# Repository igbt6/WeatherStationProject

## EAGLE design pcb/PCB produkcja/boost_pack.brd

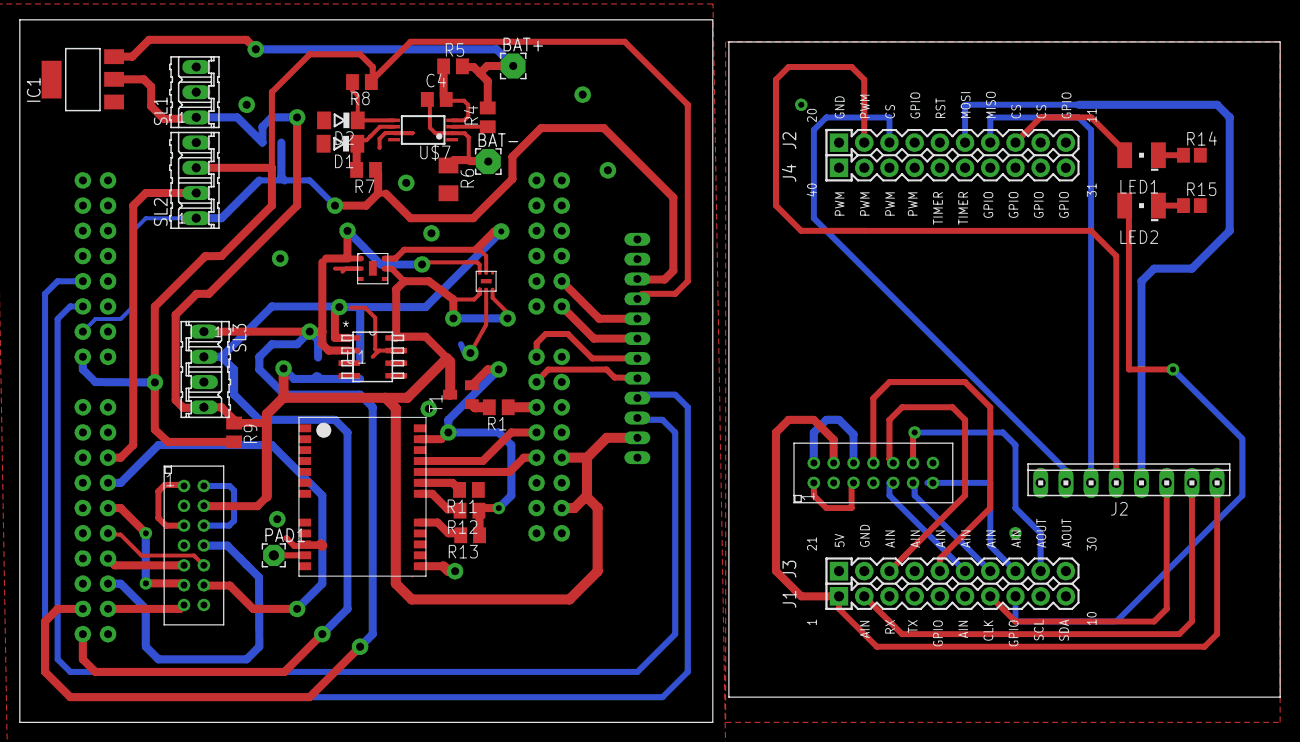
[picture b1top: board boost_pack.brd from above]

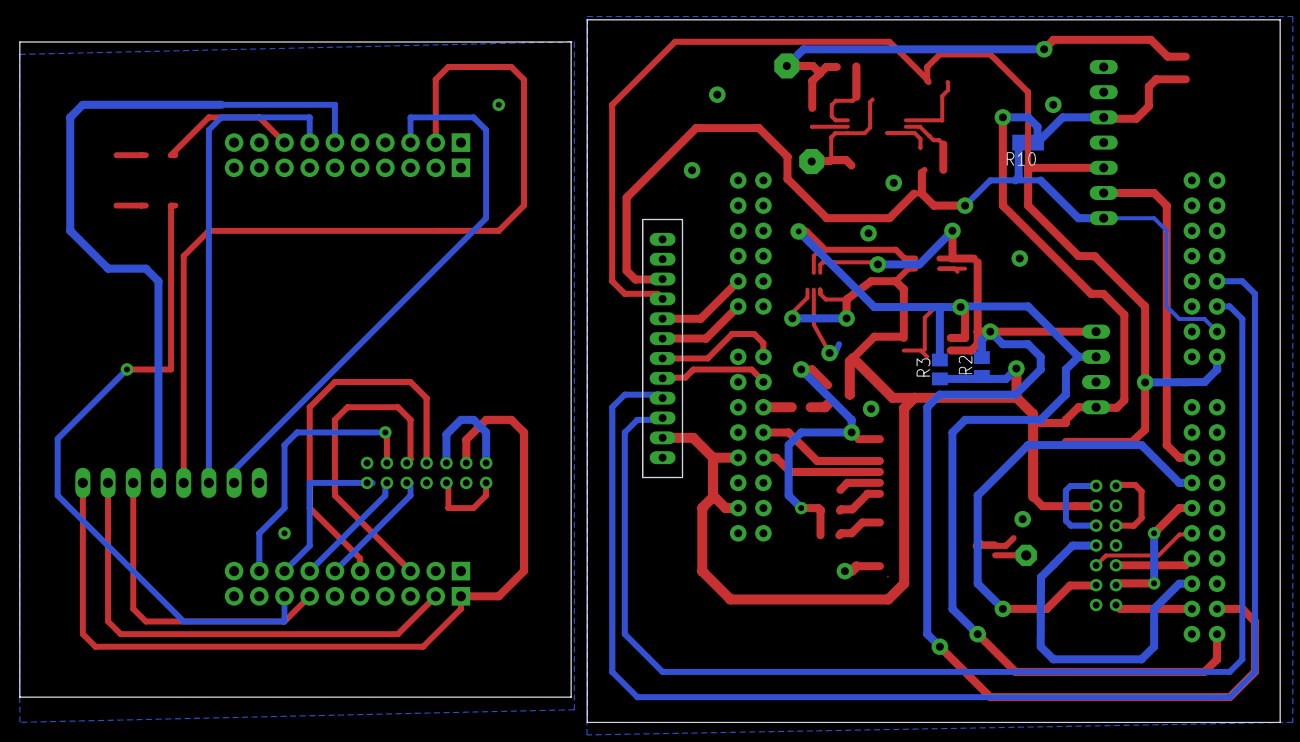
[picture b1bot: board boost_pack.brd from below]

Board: 2 copper layers, 127.0 x 70.8 mm, 39 parts (3 on the bottom side), 56 nets.

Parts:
A1: 4X10-BOOSTERPACK
BAT+: 2,54/0,8
BAT-: 2,54/0,8
C4: 100n; C0805
D1, D2: 5V6; SOD80C
IC1: REG1117; SOT223
J2: 10X08MTA
LED1, LED2: LG_T679-E1F1-1; PLCC2
PAD1: 2,15/1,0
R1, R11, R12, R13: 1K; M0805
R2, R3, R9, R10: 10K; M0805
R4: 1k; M0805
R5: 500R; M0805
R6: 20m; M1206
R7, R8: 150R; M0805
R14, R15: R0805
SL1: 03P
SL2, SL3: 04P
T1: SOT23-BCE
U1: ADT7410TRZ; R_8
U$1: INTO_CON
U$2: GTS-4E-60
U$3, U$8: 2X7PIN; 2X7PINCON
U$4: SI7020-A10; DFN6(3X3MM)
U$5: 12PINCON; 12PIN2MMCON
U$6: MAX44006; 6OTDFN
U$7: DS2782; TSSOP8

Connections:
+3V3: A1.1, J2.1, U$8.P$13
+5V/1: IC1.2, R2.1, R3.1, R9.1, R10.1, SL1.1, SL3.4, T1.E, U1.8, U$1.P$39, U$1.P$43, U$3.P$13, U$4.P$5, U$5.P$2, U$6.P1, U$6.P3
GND: D1.A, D2.A, IC1.1, R6.2, R11.1, SL2.4, SL3.3, U1.3, U1.4, U1.7, U$1.P$30, U$1.P$47, U$1.P$49, U$2.A10, U$2.A12, U$2.A13, U$2.A24, U$3.P$2, U$3.P$8, U$4.P$2, U$5.P$1, U$6.P2, U$7.7
GND1: A1.20, A1.22, J2.8, R14.2, R15.2, U$8.P$2, U$8.P$8
INTER: SL2.2, U$1.P$21
unnamed: U$1.P$46, U$2.A21
unnamed: U$8.P$12, U$8.P$14
unnamed: U$1.P$52, U$5.P$6
unnamed: PAD1.1, U$2.A11
unnamed: U$1.P$50, U$5.P$5
unnamed: U$1.P$53, U$5.P$7
unnamed: U$1.P$55, U$5.P$8
unnamed: U$1.P$12, U$5.P$3
unnamed: U$1.P$10, U$5.P$4
unnamed: C4.2, R5.1, U$7.4
unnamed: BAT-.1, C4.1, R6.1, U$7.2
unnamed: R4.1, U$7.3
unnamed: D1.C, R7.2, U$7.6
unnamed: D2.C, R8.2, U$7.5
unnamed: U$3.P$1, U$3.P$3
unnamed: U$3.P$12, U$3.P$14
unnamed: U$1.P$25, U$3.P$6
unnamed: U$1.P$27, U$3.P$10
unnamed: BAT+.1, IC1.3, R4.2, R5.2
unnamed: U$1.P$29, U$3.P$5
unnamed: U$1.P$31, U$3.P$11
unnamed: U$1.P$23, U$3.P$9
unnamed: R12.1, R13.1, T1.C, U$2.A23
unnamed: R1.1, U$1.P$48
unnamed: R1.2, T1.B
unnamed: U$1.P$33, U$3.P$7
unnamed: U$1.P$44, U$2.A20
unnamed: R12.2, U$2.A18
unnamed: R11.2, U$2.A19
unnamed: R13.2, U$2.A17
unnamed: U$8.P$1, U$8.P$3
unnamed: LED1.C, R14.1
unnamed: LED2.C, R15.1
PA4: A1.13, LED1.A
PA5: A1.8, LED2.A
PB2: A1.19, J2.5
PB4: A1.7, J2.3
PB5: A1.2, J2.2
PB6: A1.14, J2.6
PB7: A1.15, J2.4
PD0: A1.23, U$8.P$10
PD2: A1.25, U$8.P$11
PD3: A1.26, U$8.P$5
PE0: A1.18, J2.7
PE1: A1.27, U$8.P$6
PE2: A1.28, U$8.P$7
PE3: A1.29, U$8.P$9
SCL1: R3.2, SL3.2, U1.1, U$1.P$36, U$4.P$6, U$6.P5
SCL2: R7.1, R10.2, SL2.1, U$1.P$14, U$5.P$10
SDA1: R2.2, SL3.1, U1.2, U$1.P$34, U$4.P$1, U$6.P6
SDA2: R8.1, R9.2, SL2.3, U$1.P$16, U$5.P$9

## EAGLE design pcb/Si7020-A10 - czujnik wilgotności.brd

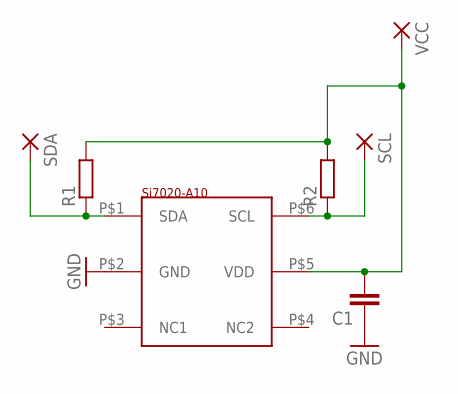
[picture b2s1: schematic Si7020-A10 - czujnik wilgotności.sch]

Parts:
C1: C-EUC0805; C0805
R1, R2: R-EU_M0805; M0805
SCL: 2,54/0,9
SDA: 2,54/0,9
U$1: SI7020-A10; DFN6(3X3MM)
VCC: 2,54/0,9

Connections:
GND: C1.1, U$1.P$2 (GND)
unnamed: C1.2, R1.2, R2.2, U$1.P$5 (VDD), VCC.1
unnamed: R2.1, SCL.1, U$1.P$6 (SCL)
unnamed: R1.1, SDA.1, U$1.P$1 (SDA)

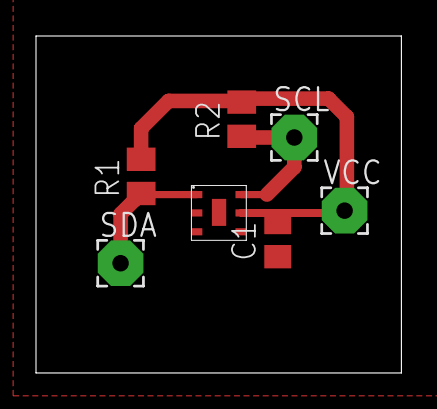
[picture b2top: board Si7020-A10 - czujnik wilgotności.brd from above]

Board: 2 copper layers, 20.3 x 18.7 mm, 7 parts (0 on the bottom side), 4 nets.

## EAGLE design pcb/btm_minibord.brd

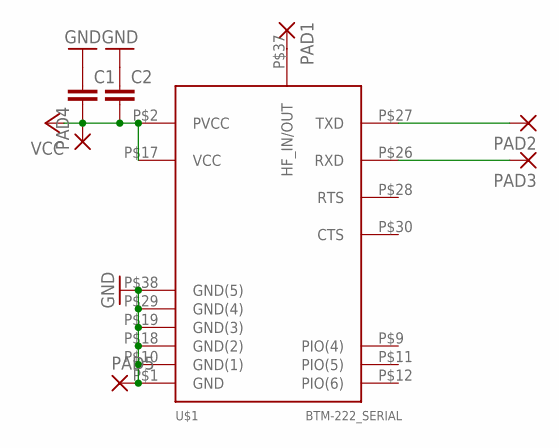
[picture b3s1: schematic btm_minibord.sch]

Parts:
C1, C2: C-EUC0805; C0805
PAD1, PAD2, PAD3, PAD4, PAD5: 1,6/0,8
U$1: BTM-222_SERIAL; BTM-222

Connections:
GND: C1.1, C2.1, PAD5.1, U$1.P$1 (GND), U$1.P$10 (GND(1)), U$1.P$18 (GND(2)), U$1.P$19 (GND(3)), U$1.P$29 (GND(4)), U$1.P$38 (GND(5))
unnamed: PAD2.1, U$1.P$27 (TXD)
unnamed: PAD3.1, U$1.P$26 (RXD)
unnamed: PAD1.1, U$1.P$37 (HF_IN/OUT)
VCC: C1.2, C2.2, PAD4.1, U$1.P$2 (PVCC), U$1.P$17 (VCC)

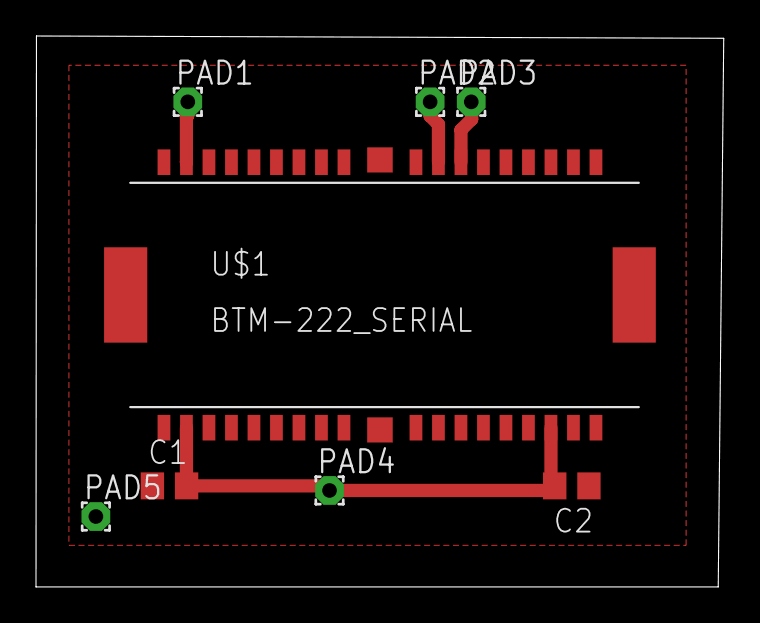
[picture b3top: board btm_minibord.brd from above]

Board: 2 copper layers, 38.2 x 30.6 mm, 8 parts (0 on the bottom side), 5 nets.

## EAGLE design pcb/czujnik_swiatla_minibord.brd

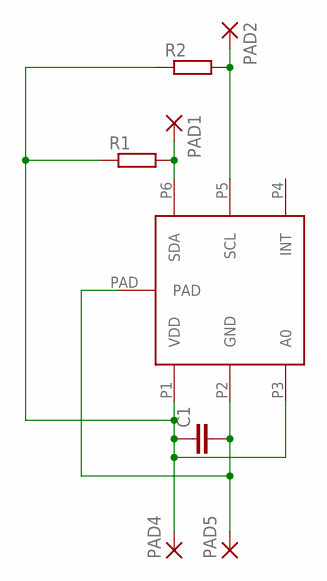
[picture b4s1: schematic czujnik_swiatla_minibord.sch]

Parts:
C1: C-EUC0805; C0805
PAD1, PAD2, PAD4, PAD5: 1,6/0,8
R1, R2: R-EU_R0805; R0805
U$1: MAX44006; 6OTDFN

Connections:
unnamed: PAD2.1, R2.2, U$1.P5 (SCL)
unnamed: PAD1.1, R1.2, U$1.P6 (SDA)
unnamed: C1.1, PAD4.1, R1.1, R2.1, U$1.P1 (VDD), U$1.P3 (A0)
unnamed: C1.2, PAD5.1, U$1.P2 (GND), U$1.PAD

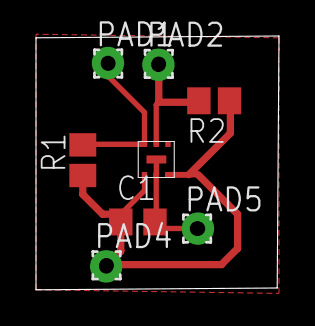
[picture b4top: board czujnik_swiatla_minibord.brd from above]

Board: 2 copper layers, 13.5 x 14.1 mm, 8 parts (0 on the bottom side), 4 nets.

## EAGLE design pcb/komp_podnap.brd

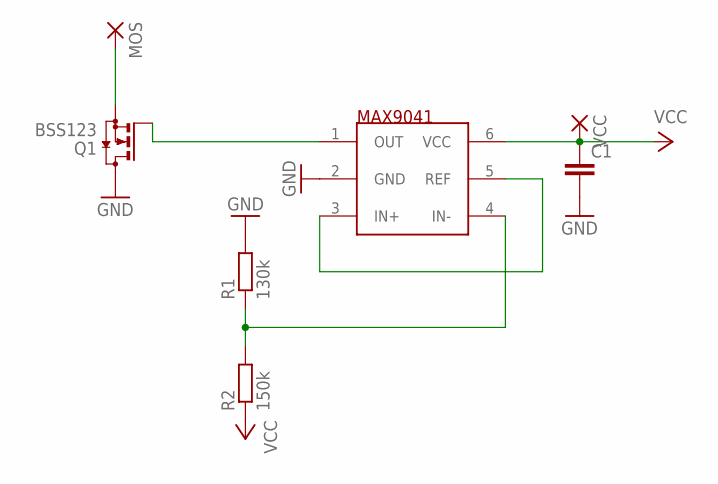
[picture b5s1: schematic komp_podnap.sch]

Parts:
C1: C-EUC0805; C0805
MOS: 2,54/0,8
Q1: BSS123; SOT23
R1: 130k; M0805
R2: 150k; M0805
U$1: MAX9041; SOT23-6
VCC: 2,54/0,8

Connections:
GND: C1.2, Q1.3 (D), R1.2, U$1.2 (GND)
unnamed: U$1.3 (IN+), U$1.5 (REF)
unnamed: R1.1, R2.2, U$1.4 (IN-)
unnamed: Q1.1 (G), U$1.1 (OUT)
unnamed: MOS.1, Q1.2 (S)
VCC: C1.1, R2.1, U$1.6 (VCC), VCC.1

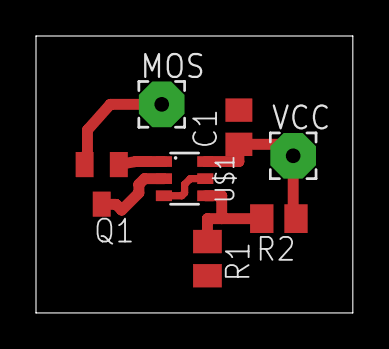
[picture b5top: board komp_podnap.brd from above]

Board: 2 copper layers, 17.6 x 15.4 mm, 7 parts (0 on the bottom side), 6 nets.

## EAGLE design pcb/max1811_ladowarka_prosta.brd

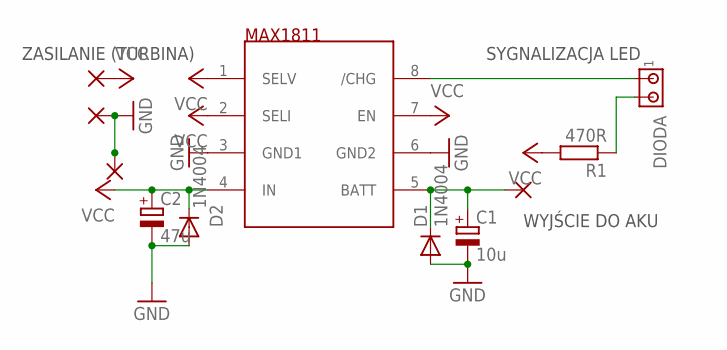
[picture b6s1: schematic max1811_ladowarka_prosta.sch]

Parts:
BATERIA: 1,6/0,9
C1: 10u; E2,5-6
C2: 47u; E2,5-6
D1, D2: 1N4004; DO41-10
DIODA: MTA02-100; 10X02MTA
PAD2, PAD4: 1,6/0,9
R1: 470R; R0805
U$1: MAX1811; SO-08
WEJ: 1,6/0,9

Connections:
GND: C1.-, C2.-, D1.A, D2.A, PAD2.1, PAD4.1, U$1.3 (GND1), U$1.6 (GND2)
unnamed: DIODA.1, U$1.8 (/CHG)
unnamed: DIODA.2, R1.1
unnamed: BATERIA.1, C1.+, D1.C, U$1.5 (BATT)
VCC: C2.+, D2.C, R1.2, U$1.1 (SELV), U$1.2 (SELI), U$1.4 (IN), U$1.7 (EN), WEJ.1

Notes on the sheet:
ZASILANIE (TURBINA)
WYJŚCIE DO AKU
SYGNALIZACJA LED

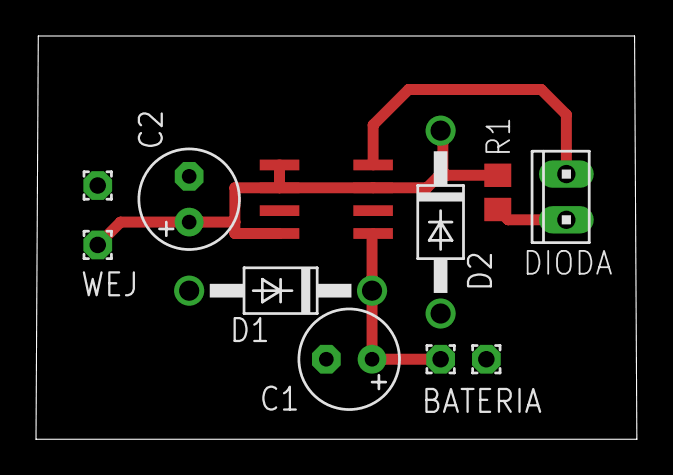
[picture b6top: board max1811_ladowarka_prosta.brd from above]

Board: 2 copper layers, 33.4 x 22.4 mm, 11 parts (0 on the bottom side), 5 nets.

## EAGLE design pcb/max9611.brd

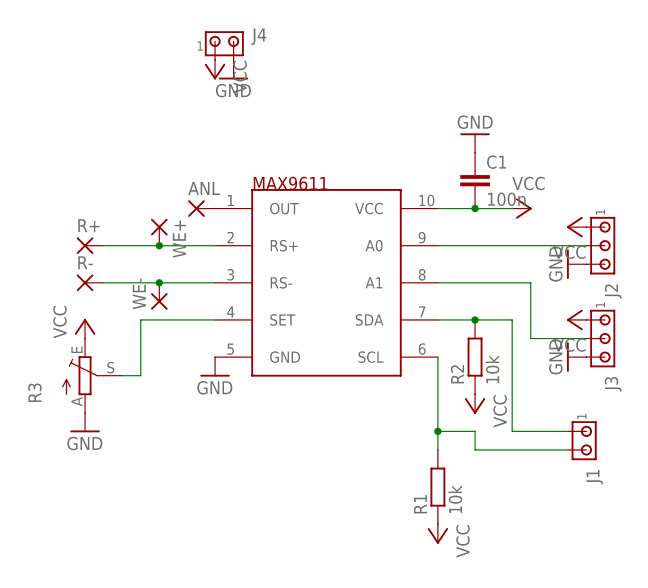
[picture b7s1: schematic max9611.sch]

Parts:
ANL: 1,6/0,8
C1: 100n; C0805
J1, J4: MTA02-100; 10X02MTA
J2, J3: MTA03-100; 10X03MTA
R1, R2: 10k; M0805
R3: TRIM_EU-RJ9W; RJ9W
R+: 1,6/0,8
R-: 1,6/0,8
U$1: MAX9611; UMAX10
WE+: 1,6/0,8
WE-: 1,6/0,8

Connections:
GND: C1.1, J2.3, J3.3, J4.2, R3.A, U$1.5 (GND)
unnamed: J2.2, U$1.9 (A0)
unnamed: J3.2, U$1.8 (A1)
unnamed: J1.1, R2.2, U$1.7 (SDA)
unnamed: J1.2, R1.2, U$1.6 (SCL)
unnamed: ANL.1, U$1.1 (OUT)
unnamed: R3.S, U$1.4 (SET)
unnamed: R+.1, U$1.2 (RS+), WE+.1
unnamed: R-.1, U$1.3 (RS-), WE-.1
VCC: C1.2, J2.1, J3.1, J4.1, R1.1, R2.1, R3.E, U$1.10 (VCC)

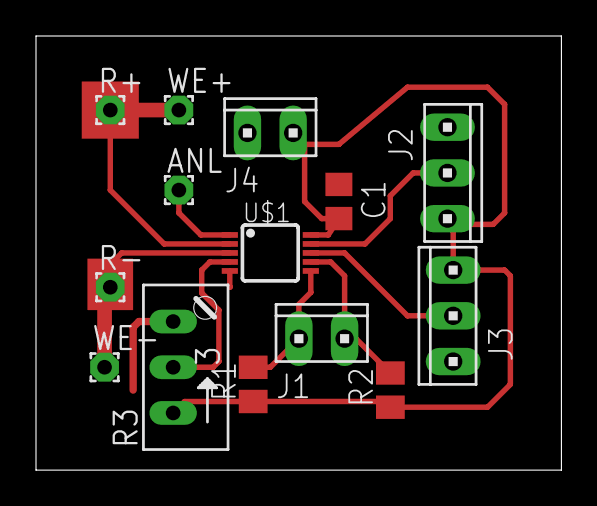
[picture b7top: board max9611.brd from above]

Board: 2 copper layers, 29.2 x 24.1 mm, 14 parts (0 on the bottom side), 10 nets.

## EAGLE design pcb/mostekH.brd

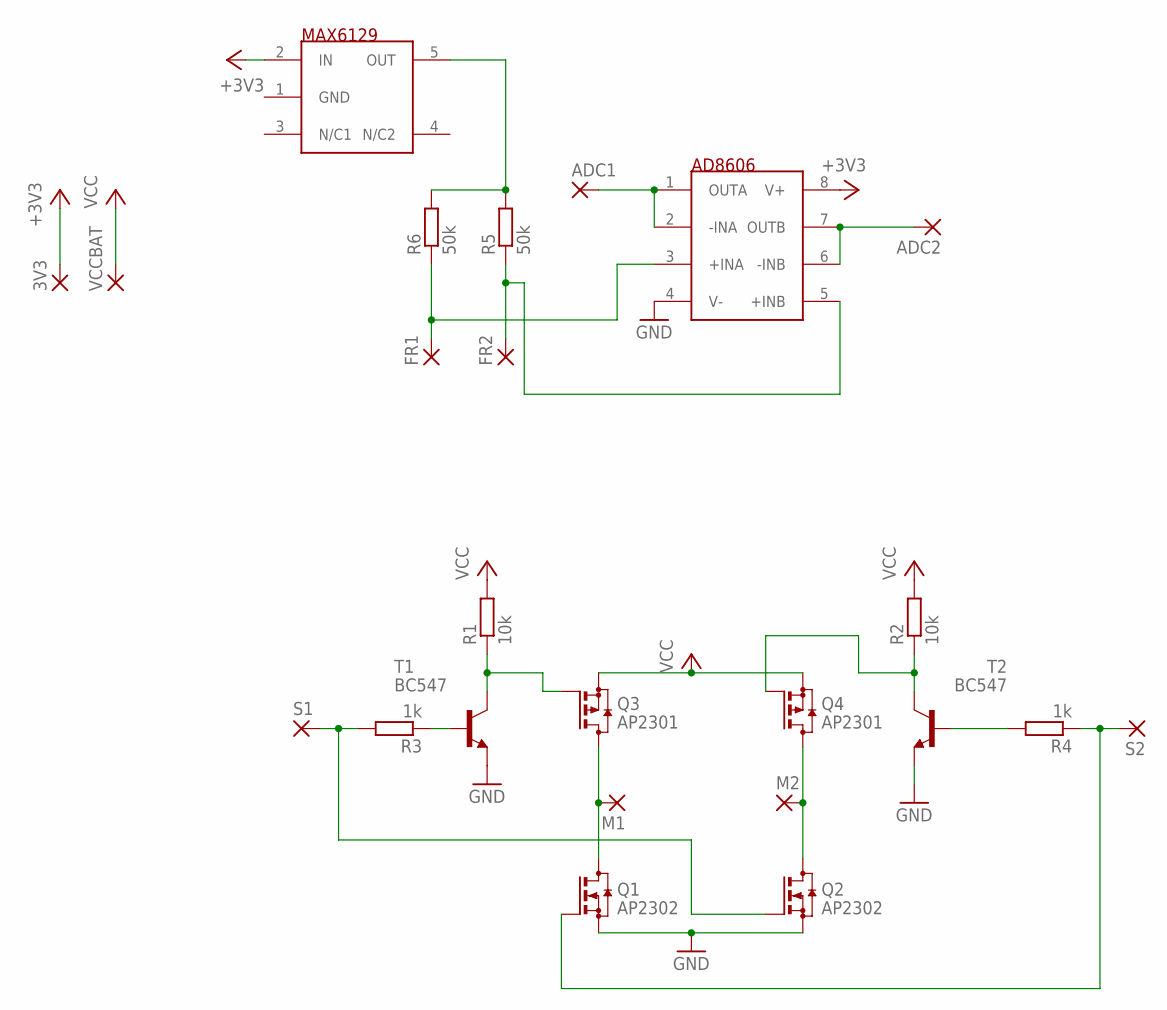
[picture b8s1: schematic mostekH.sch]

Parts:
3V3: 2,54/0,8
ADC1, ADC2: 2,54/0,8
FR1, FR2: 2,54/0,8
M1, M2: 2,54/0,8
Q1, Q2: AP2302; SOT23
Q3, Q4: AP2301; SOT23
R1, R2: 10k; M0805
R3, R4: 1k; M0805
R5, R6: 50k; M0805
S1, S2: 2,54/0,8
T1, T2: BC547; TO92
U$1: AD8606; SOIC8
U$2: MAX6129; SOT23-5L
VCCBAT: 2,54/0,8

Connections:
+3V3: 3V3.1, U$1.8 (V+), U$2.2 (IN)
GND: Q1.2 (S), Q2.2 (S), T1.1 (E), T2.1 (E), U$1.4 (V-)
unnamed: M1.1, Q1.3 (D), Q3.3 (D)
unnamed: M2.1, Q2.3 (D), Q4.3 (D)
unnamed: Q3.1 (G), R1.1, T1.3 (C)
unnamed: Q4.1 (G), R2.1, T2.3 (C)
unnamed: R4.2, T2.2 (B)
unnamed: FR1.1, R6.1, U$1.3 (+INA)
unnamed: Q2.1 (G), R3.2, S1.1
unnamed: FR2.1, R5.1, U$1.5 (+INB)
unnamed: Q1.1 (G), R4.1, S2.1
unnamed: R3.1, T1.2 (B)
unnamed: ADC1.1, U$1.1 (OUTA), U$1.2 (-INA)
unnamed: ADC2.1, U$1.6 (-INB), U$1.7 (OUTB)
unnamed: R5.2, R6.2, U$2.5 (OUT)
VCC: Q3.2 (S), Q4.2 (S), R1.2, R2.2, VCCBAT.1

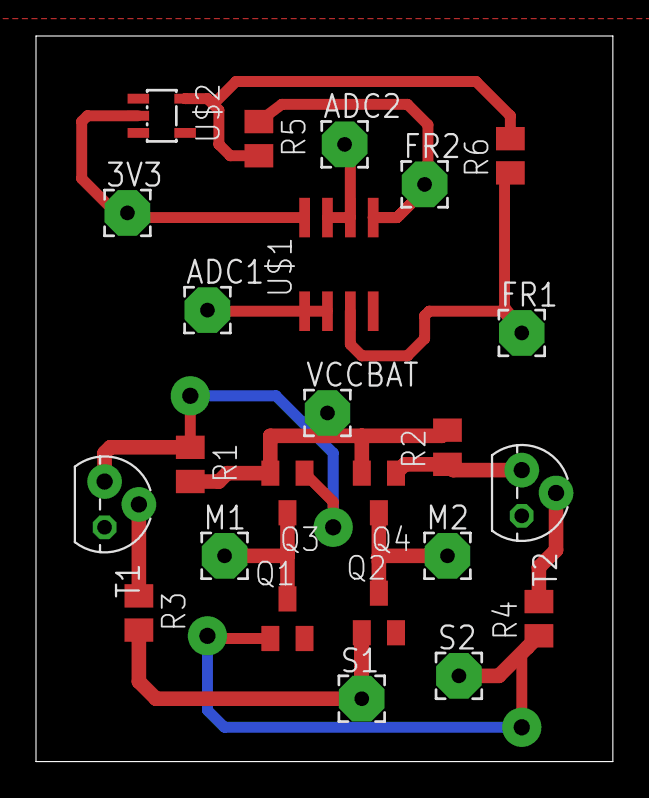
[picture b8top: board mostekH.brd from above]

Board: 2 copper layers, 32.0 x 40.3 mm, 24 parts (0 on the bottom side), 16 nets.
